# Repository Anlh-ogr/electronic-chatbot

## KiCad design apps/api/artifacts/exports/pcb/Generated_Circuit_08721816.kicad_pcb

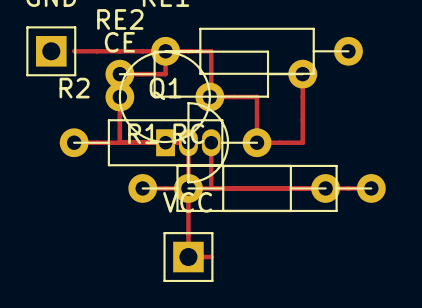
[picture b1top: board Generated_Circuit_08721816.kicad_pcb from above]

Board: 2 copper layers, 9 parts (0 on the bottom side), 5 nets.

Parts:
CE: CAPACITOR; CP_Radial_D5.0mm_P2.50mm
GND: POWER_SYMBOL; N/A
Q1: BJT_NPN; TO-92_Inline
R1, R2: RESISTOR; R_Axial_DIN0207_L6.3mm_D2.5mm_P10.16mm_Horizontal
RC: RESISTOR; R_Axial_DIN0207_L6.3mm_D2.5mm_P10.16mm_Horizontal
RE1, RE2: RESISTOR; R_Axial_DIN0207_L6.3mm_D2.5mm_P10.16mm_Horizontal
VCC: POWER_SYMBOL; N/A

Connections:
0: CE.2, GND.1, R2.2, RE2.2
BASE: Q1.2, R1.2, R2.1
COL: Q1.3, RC.2
EMIT: CE.1, Q1.1, RE1.1, RE2.1
VCC: R1.1, RC.1, VCC.1

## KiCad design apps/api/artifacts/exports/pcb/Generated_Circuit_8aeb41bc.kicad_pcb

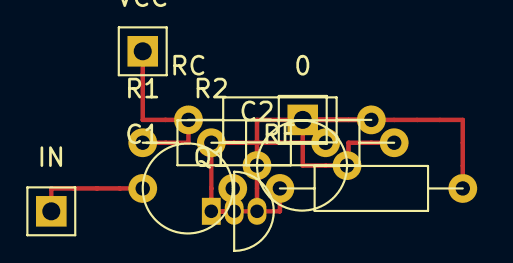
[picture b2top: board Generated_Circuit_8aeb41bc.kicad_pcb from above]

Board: 2 copper layers, 10 parts (0 on the bottom side), 6 nets.

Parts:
0: CONNECTOR; PinHeader_1x01_P2.54mm_Vertical
C1, C2: CAPACITOR; CP_Radial_D5.0mm_P2.50mm
IN: CONNECTOR; PinHeader_1x01_P2.54mm_Vertical
Q1: BJT_NPN; TO-92_Inline
R1, R2: RESISTOR; R_Axial_DIN0207_L6.3mm_D2.5mm_P10.16mm_Horizontal
RC: RESISTOR; R_Axial_DIN0207_L6.3mm_D2.5mm_P10.16mm_Horizontal
RE: RESISTOR; R_Axial_DIN0207_L6.3mm_D2.5mm_P10.16mm_Horizontal
VCC: CONNECTOR; PinHeader_1x01_P2.54mm_Vertical

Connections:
0: 0.1, C2.2, R2.2, RE.2
BASE: C1.2, Q1.2, R1.2, R2.1
COL: C2.1, Q1.3, RC.2
EMIT: Q1.1, RE.1
IN: C1.1, IN.1
VCC: R1.1, RC.1, VCC.1

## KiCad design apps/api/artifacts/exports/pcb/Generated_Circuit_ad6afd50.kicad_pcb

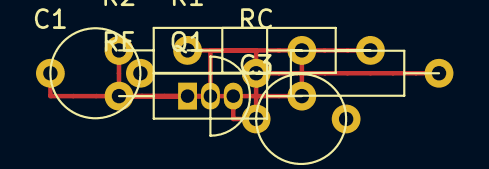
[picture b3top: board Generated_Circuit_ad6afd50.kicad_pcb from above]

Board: 2 copper layers, 7 parts (0 on the bottom side), 5 nets.

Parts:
C1, C3: CAPACITOR; CP_Radial_D5.0mm_P2.50mm
Q1: BJT_NPN; TO-92_Inline
R1, R2: RESISTOR; R_Axial_DIN0207_L6.3mm_D2.5mm_P10.16mm_Horizontal
RC: RESISTOR; R_Axial_DIN0207_L6.3mm_D2.5mm_P10.16mm_Horizontal
RE: RESISTOR; R_Axial_DIN0207_L6.3mm_D2.5mm_P10.16mm_Horizontal

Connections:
0: C1.1, R2.2, RE.2
BASE: Q1.2, R1.2, R2.1
COLL: C3.1, Q1.3, RC.2
EMIT: Q1.1, RE.1
VCC: R1.1, RC.1

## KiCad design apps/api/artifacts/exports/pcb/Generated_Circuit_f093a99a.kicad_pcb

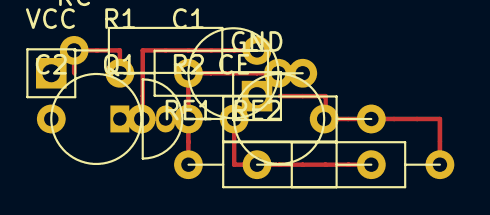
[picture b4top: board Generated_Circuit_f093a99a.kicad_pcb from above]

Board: 2 copper layers, 11 parts (0 on the bottom side), 6 nets.

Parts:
C1, C2: CAPACITOR; CP_Radial_D5.0mm_P2.50mm
CE: CAPACITOR; CP_Radial_D6.3mm_P2.50mm
GND: POWER_SYMBOL; PinHeader_1x01_P2.54mm_Vertical
Q1: BJT_NPN; TO-92_Inline
R1, R2: RESISTOR; R_Axial_DIN0207_L6.3mm_D2.5mm_P10.16mm_Horizontal
RC: RESISTOR; R_Axial_DIN0207_L6.3mm_D2.5mm_P10.16mm_Horizontal
RE1, RE2: RESISTOR; R_Axial_DIN0207_L6.3mm_D2.5mm_P10.16mm_Horizontal
VCC: POWER_SYMBOL; PinHeader_1x01_P2.54mm_Vertical

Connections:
0: CE.2, GND.1, R2.2, RE2.2
+12V: R1.1, RC.1, VCC.1
N-Q1-B: C1.2, Q1.2, R1.2, R2.1
N-Q1-C: C2.2, Q1.1, RC.2
N-Q1-E: Q1.3, RE1.1
N-RE-SPLIT: CE.1, RE1.2, RE2.1

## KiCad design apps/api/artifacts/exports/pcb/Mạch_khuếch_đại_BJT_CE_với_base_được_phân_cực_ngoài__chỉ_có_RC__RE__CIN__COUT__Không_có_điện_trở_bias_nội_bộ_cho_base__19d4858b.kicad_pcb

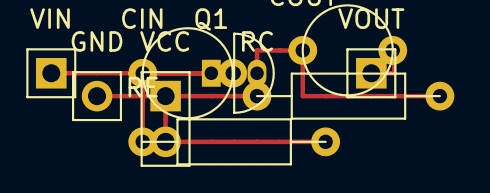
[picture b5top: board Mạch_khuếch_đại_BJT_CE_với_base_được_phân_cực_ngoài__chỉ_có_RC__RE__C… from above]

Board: 2 copper layers, 9 parts (0 on the bottom side), 7 nets.

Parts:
CIN: CAPACITOR; CP_Radial_D5.0mm_P2.50mm
COUT: CAPACITOR; CP_Radial_D5.0mm_P2.50mm
GND: GROUND; PinHeader_1x01_P2.54mm_Vertical
Q1: BJT; TO-92_Inline
RC: RESISTOR; R_Axial_DIN0207_L6.3mm_D2.5mm_P10.16mm_Vertical
RE: RESISTOR; R_Axial_DIN0207_L6.3mm_D2.5mm_P10.16mm_Vertical
VCC: VOLTAGE_SOURCE; PinHeader_1x02_P2.54mm_Vertical
VIN: PORT; PinHeader_1x01_P2.54mm_Vertical
VOUT: PORT; PinHeader_1x01_P2.54mm_Vertical

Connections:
net_base: CIN.1, Q1.2
net_collector: COUT.1, Q1.3, RC.2
net_emitter: Q1.1, RE.1
net_gnd: GND.1, RE.2, VCC.2
net_in: CIN.2, VIN.1
net_out: COUT.2, VOUT.1
net_vcc: RC.1, VCC.1
